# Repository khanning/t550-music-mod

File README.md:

FreeCAD and Eagle files for my modular music kit I created for Harvard University's Graduate School of Education class T550, Designing for Learning by Creating.

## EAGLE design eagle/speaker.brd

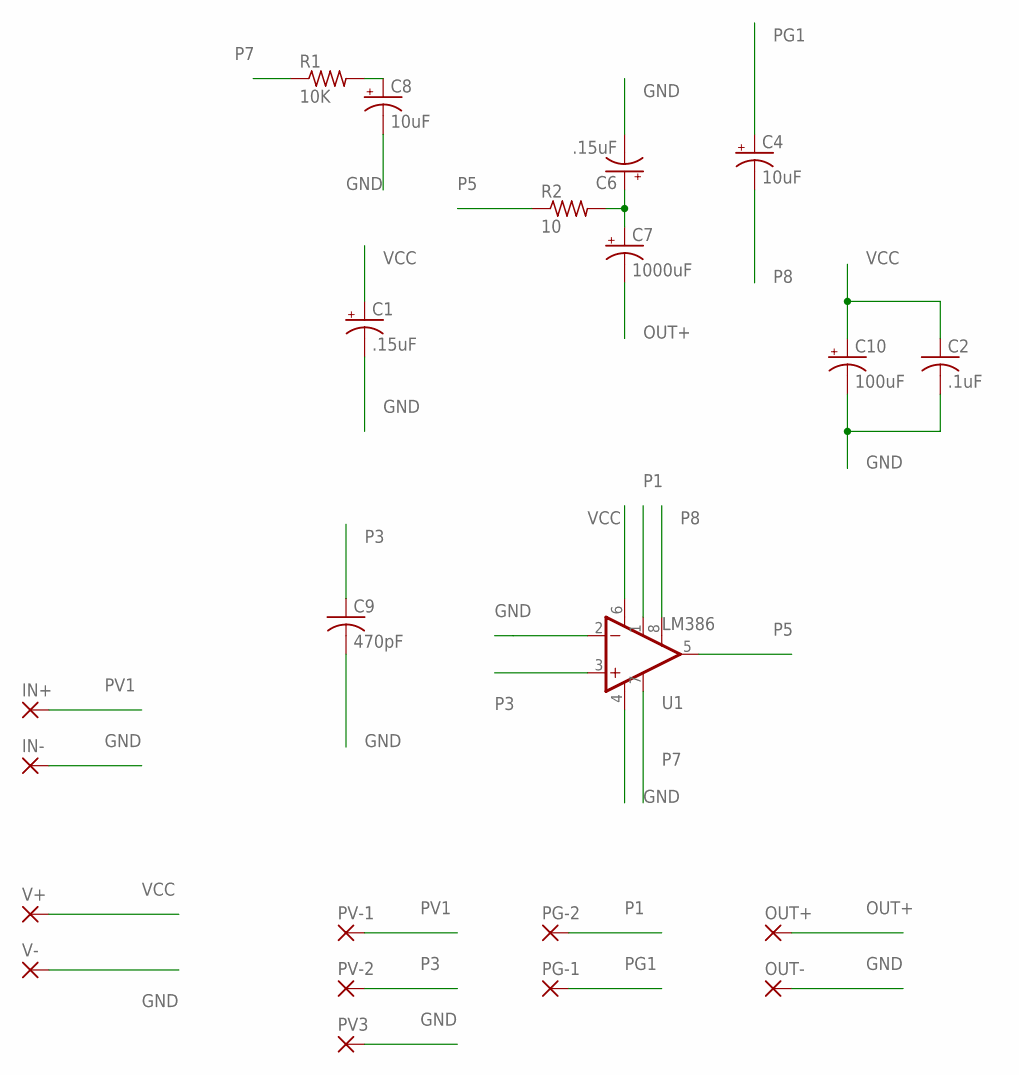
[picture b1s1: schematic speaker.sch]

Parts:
C1, C6: .15uF; B45181A
C2: .1uF; C025-024X044
C4: 10uF; E3,5-4
C7: 1000uF; E5-10,5
C8: 10uF; E1,8-4
C9: 470pF; C050-025X075
C10: 100uF; E2-5
IN+: 2,54/1,0
IN-: 2,54/1,0
OUT+: 2,54/1,0
OUT-: 2,54/1,0
PG-1, PG-2: 2,54/1,0
PV3: 2,54/1,0
PV-1, PV-2: 2,54/1,0
R1: 10K; 0207/7
R2: 10; 0207/7
U1: LM386; DIP08
V+: 2,54/1,0
V-: 2,54/1,0

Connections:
GND: C1.-, C2.2, C6.-, C8.-, C9.2, C10.-, IN-.1, OUT-.1, PV3.1, U1.2 (-IN), U1.4 (V-), V-.1
unnamed: C6.+, C7.+, R2.2
unnamed: C8.+, R1.2
OUT+: C7.-, OUT+.1
P1: PG-2.1, U1.1 (GAIN)
P3: C9.1, PV-2.1, U1.3 (+IN)
P5: R2.1, U1.5 (OUT)
P7: R1.1, U1.7 (BP)
P8: C4.-, U1.8 (GAIN)
PG1: C4.+, PG-1.1
PV1: IN+.1, PV-1.1
VCC: C1.+, C2.1, C10.+, U1.6 (V+), V+.1

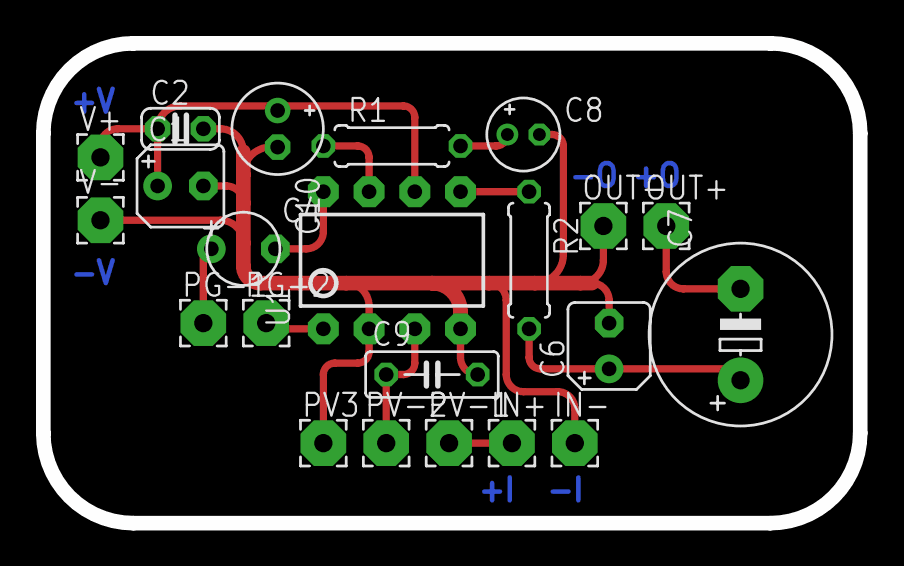
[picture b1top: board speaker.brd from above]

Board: 2 copper layers, 45.4 x 26.7 mm, 22 parts (0 on the bottom side), 12 nets.

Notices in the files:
parts and their libraries:
SparkFun-AnalogIC: Licensing:Creative Commons ShareAlike 4.0 International - https://creativecommons.org/licenses/by-sa/4.0
